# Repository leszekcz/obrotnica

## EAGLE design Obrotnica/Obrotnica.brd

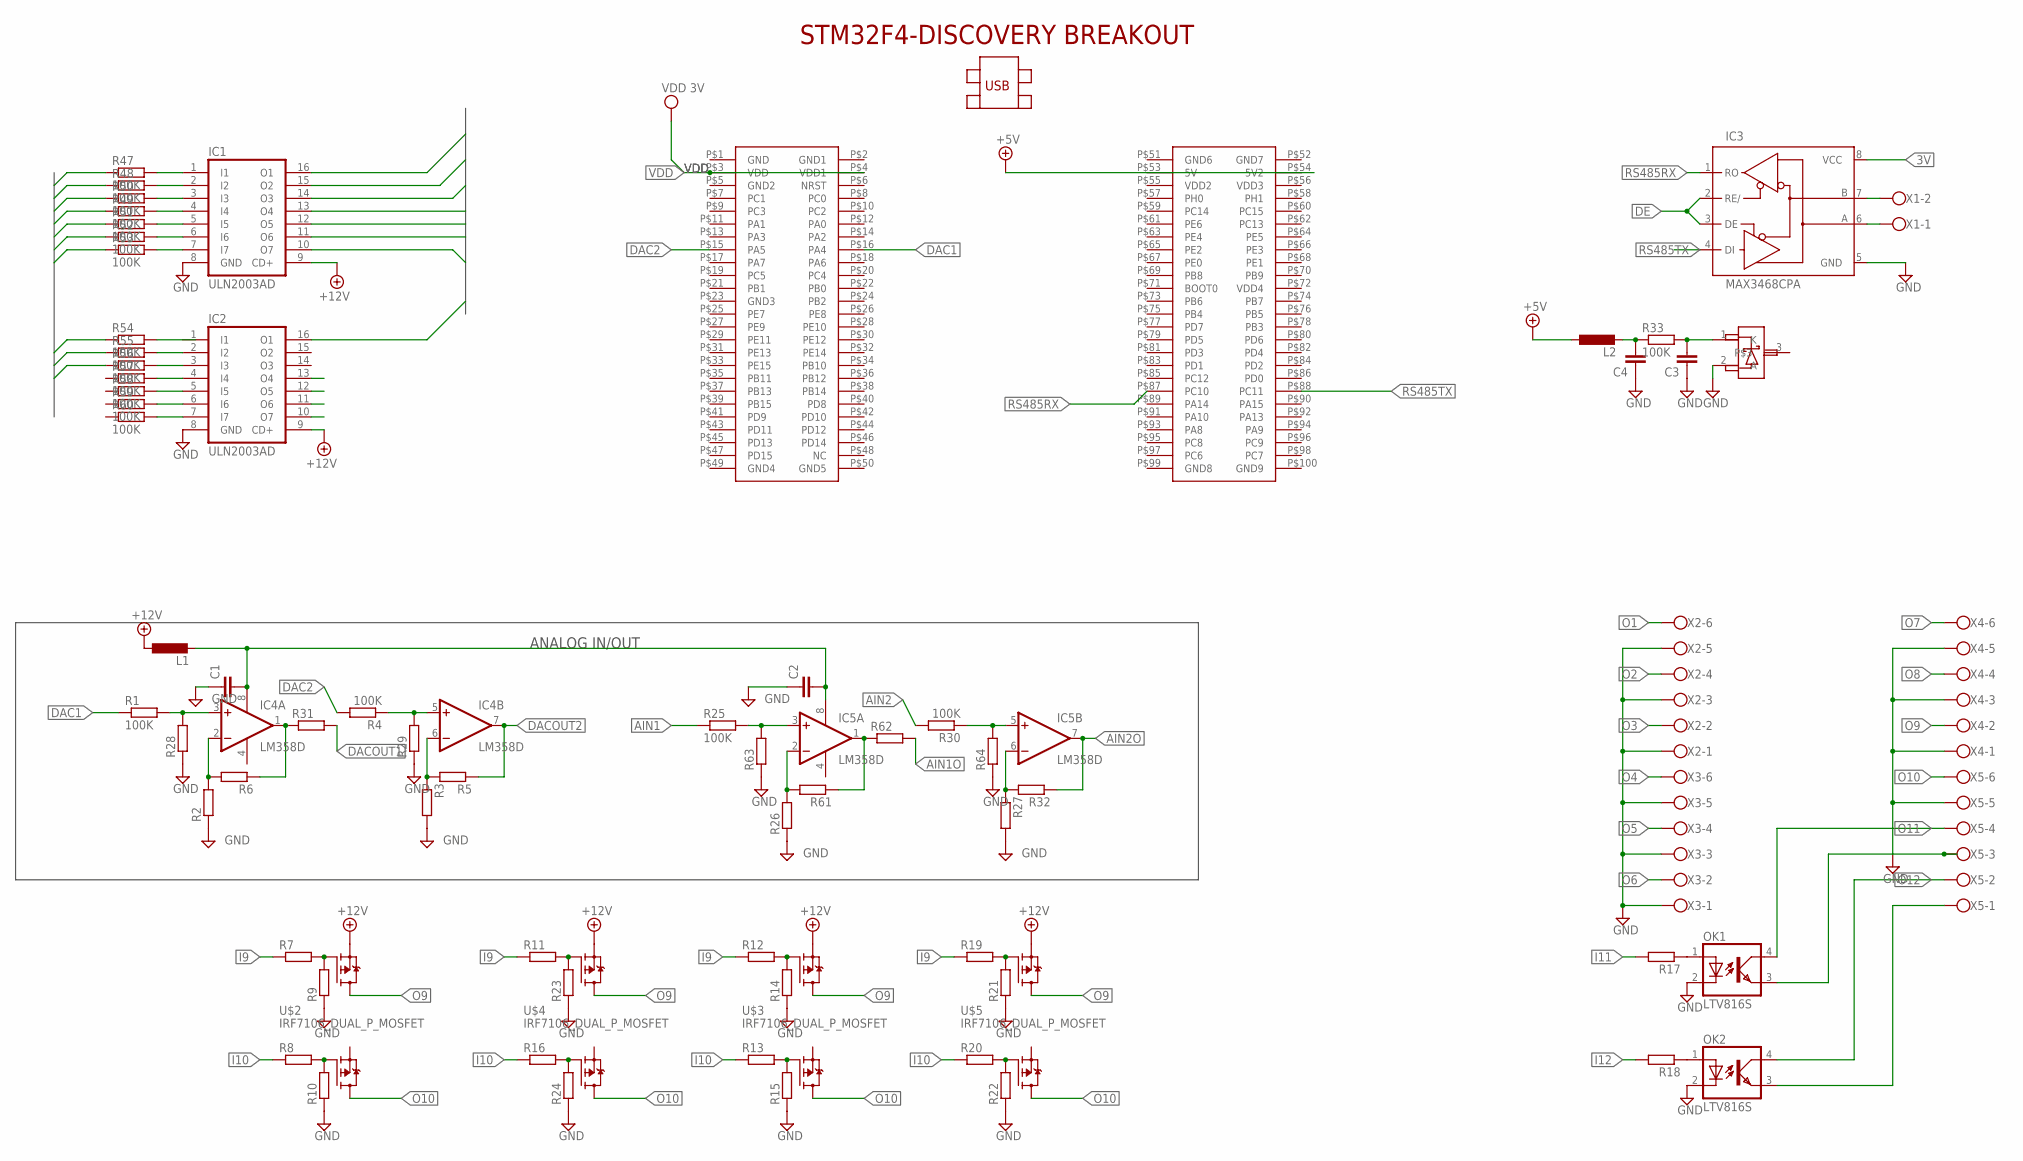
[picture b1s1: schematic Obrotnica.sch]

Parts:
C1, C2, C3, C4: C-EUC1206; C1206
IC1, IC2: ULN2003AD; SO16
IC3: MAX3468CPA; DIL08
IC4, IC5: LM358D; SO08
L1, L2: L-EU0207/7; 0207/7
OK1, OK2: LTV816S; SMD4
R1, R4, R25, R30, R33, R47, R48, R49, R50, R51, R52, R53, R54, R55, R56, R57, R58, R59, R60: 100K; R0805
R2, R3, R5, R6, R26, R27, R28, R29, R32, R61, R63, R64: R-EU_R0805; R0805
R7, R8, R9, R10, R11, R12, R13, R14, R15, R16, R17, R18, R19, R20, R21, R22, R23, R24, R31, R62: R-EU_M0805; M0805
U$1: STM32F4-DISCOVERY
U$2, U$3, U$4, U$5: IRF7106_DUAL_P_MOSFET; SO-8
U$6: LM4040_2.5V; SOT23
X1: W237-102
X2, X3, X4, X5: W237-6

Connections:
1: IC4.1 (OUT), R6.1, R31.1
2: IC5.1 (OUT), R61.1, R62.1
3V: IC3.8 (VCC)
+5V: L2.1, U$1.P$53 (5V), U$1.P$54 (5V2)
+12V: IC1.9 (CD+), IC2.9 (CD+), L1.1, U$2.1 (S), U$3.1 (S), U$4.1 (S), U$5.1 (S)
AIN1: R25.1
AIN1O: R62.2
AIN2: R30.2
AIN2O: IC5.7 (OUT), R32.1
DAC1: R1.1, U$1.P$16 (PA4)
DAC2: R4.2, U$1.P$15 (PA5)
DACOUT1: R31.2
DACOUT2: IC4.7 (OUT), R5.1
DE: IC3.2 (RE/), IC3.3 (DE)
GND: C1.1, C2.1, C3.1, C4.1, IC1.8 (GND), IC2.8 (GND), IC3.5 (GND), OK1.2 (C), OK2.2 (C), R2.1, R3.2, R9.1, R10.1, R14.1, R15.1, R21.1, R22.1, R23.1, R24.1, R26.1, R27.2, R28.1, R29.1, R63.1, R64.1, U$6.2 (A), X2.1, X2.3, X2.5, X3.1, X3.3, X3.5, X4.1, X4.3, X4.5, X5.5
I9: R7.1, R11.1, R12.1, R19.1
I10: R8.1, R13.1, R16.1, R20.1
I11: R17.2
I12: R18.2
INBUS1: R47.1
INBUS2: R48.1
INBUS3: R50.1
INBUS4: R49.1
INBUS5: R51.1
INBUS6: R52.1
INBUS7: R53.1
INBUS8: R54.1
INBUS9: R55.1
INBUS10: R56.1
unnamed: IC3.6 (A), X1.1
unnamed: IC3.7 (B), X1.2
unnamed: C1.2, C2.2, IC4.8 (V+), IC5.8 (V+), L1.2
unnamed: IC4.3 (+IN), R1.2, R28.2
unnamed: IC4.2 (-IN), R2.2, R6.2
unnamed: IC4.6 (-IN), R3.1, R5.2
unnamed: IC4.5 (+IN), R4.1, R29.2
unnamed: R7.2, R9.2, U$2.2 (G)
unnamed: R8.2, R10.2, U$2.4 (G1)
unnamed: R12.2, R14.2, U$3.2 (G)
unnamed: R13.2, R15.2, U$3.4 (G1)
unnamed: R11.2, R23.2, U$4.2 (G)
unnamed: R19.2, R21.2, U$5.2 (G)
unnamed: R20.2, R22.2, U$5.4 (G1)
unnamed: IC5.3 (+IN), R25.2, R63.2
unnamed: IC5.2 (-IN), R26.2, R61.2
unnamed: R16.2, R24.2, U$4.4 (G1)
unnamed: OK1.1 (A), R17.1
unnamed: OK2.1 (A), R18.1
unnamed: OK2.4 (COL), X5.2
unnamed: OK2.3 (EMIT), X5.1
unnamed: C3.2, R33.2, U$6.1 (K)
unnamed: C4.2, L2.2, R33.1
unnamed: IC1.1 (I1), R47.2
unnamed: IC1.2 (I2), R48.2
unnamed: IC1.3 (I3), R50.2
unnamed: IC1.4 (I4), R49.2
unnamed: IC1.5 (I5), R51.2
unnamed: IC1.6 (I6), R52.2
unnamed: IC1.7 (I7), R53.2
unnamed: IC2.2 (I2), R55.2
unnamed: IC2.3 (I3), R56.2
unnamed: IC2.4 (I4), R57.2
unnamed: IC2.5 (I5), R58.2
unnamed: IC2.6 (I6), R59.2
unnamed: IC2.7 (I7), R60.2
unnamed: IC5.6 (-IN), R27.1, R32.2
unnamed: IC5.5 (+IN), R30.1, R64.2
O1: X2.6
O2: X2.4
O3: X2.2
O4: X3.6
O5: X3.4
O6: X3.2
O7: X4.6
O8: X4.4
O9: U$2.5 (D), U$2.6 (D), U$3.5 (D), U$3.6 (D), U$4.5 (D), U$4.6 (D), U$5.5 (D), U$5.6 (D), X4.2
O10: U$2.7 (D1), U$2.8 (D1), U$3.7 (D1), U$3.8 (D1), U$4.7 (D1), U$4.8 (D1), U$5.7 (D1), U$5.8 (D1), X5.6
O11: OK1.4 (COL), X5.4
O12: OK1.3 (EMIT), X5.3
OUTBUS1: IC1.16 (O1)
OUTBUS2: IC1.15 (O2)
OUTBUS3: IC1.14 (O3)
OUTBUS4: IC1.13 (O4)
OUTBUS5: IC1.12 (O5)
OUTBUS6: IC1.11 (O6)
OUTBUS7: IC1.10 (O7)
OUTBUS8: IC2.16 (O1)
RS485RX: IC3.1 (RO), U$1.P$87 (PC10)
RS485TX: IC3.4 (DI), U$1.P$88 (PC11)
V-: IC4.4 (V-), IC5.4 (V-)
VDD: U$1.P$3 (VDD), U$1.P$4 (VDD1)

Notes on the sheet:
ANALOG IN/OUT

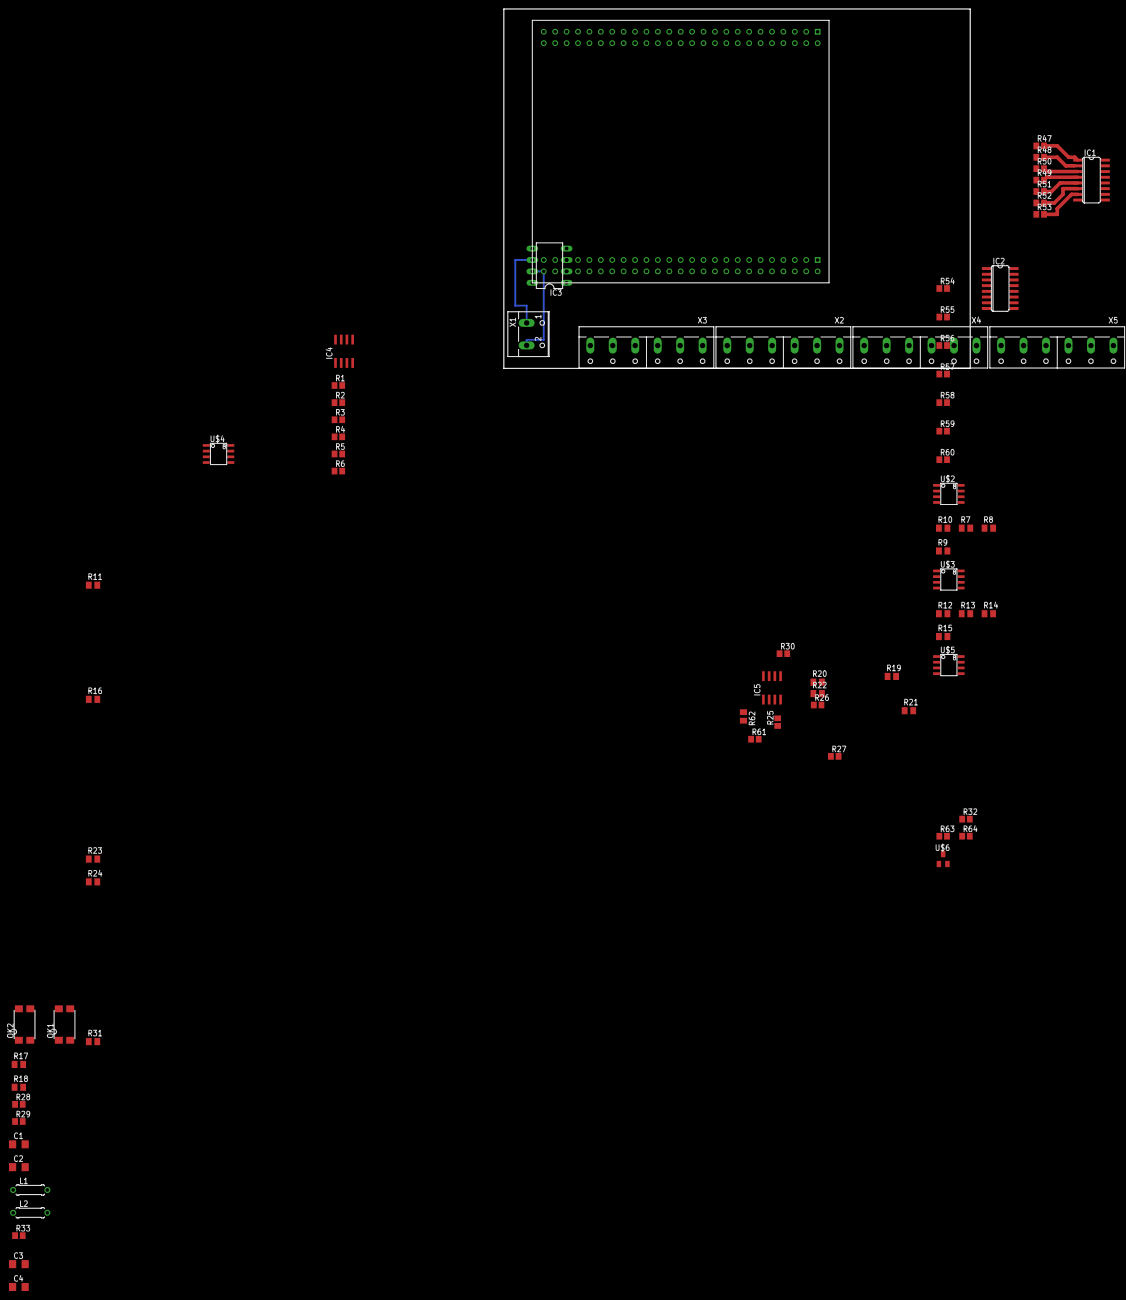
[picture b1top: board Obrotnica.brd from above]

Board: 2 copper layers, 103.8 x 80.0 mm, 75 parts (0 on the bottom side), 58 nets.

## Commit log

2014-11-14 eagle
    pliki
2014-11-14 Soft
